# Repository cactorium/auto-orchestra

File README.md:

WIP thing, honestly just publishing just in case my laptop dies

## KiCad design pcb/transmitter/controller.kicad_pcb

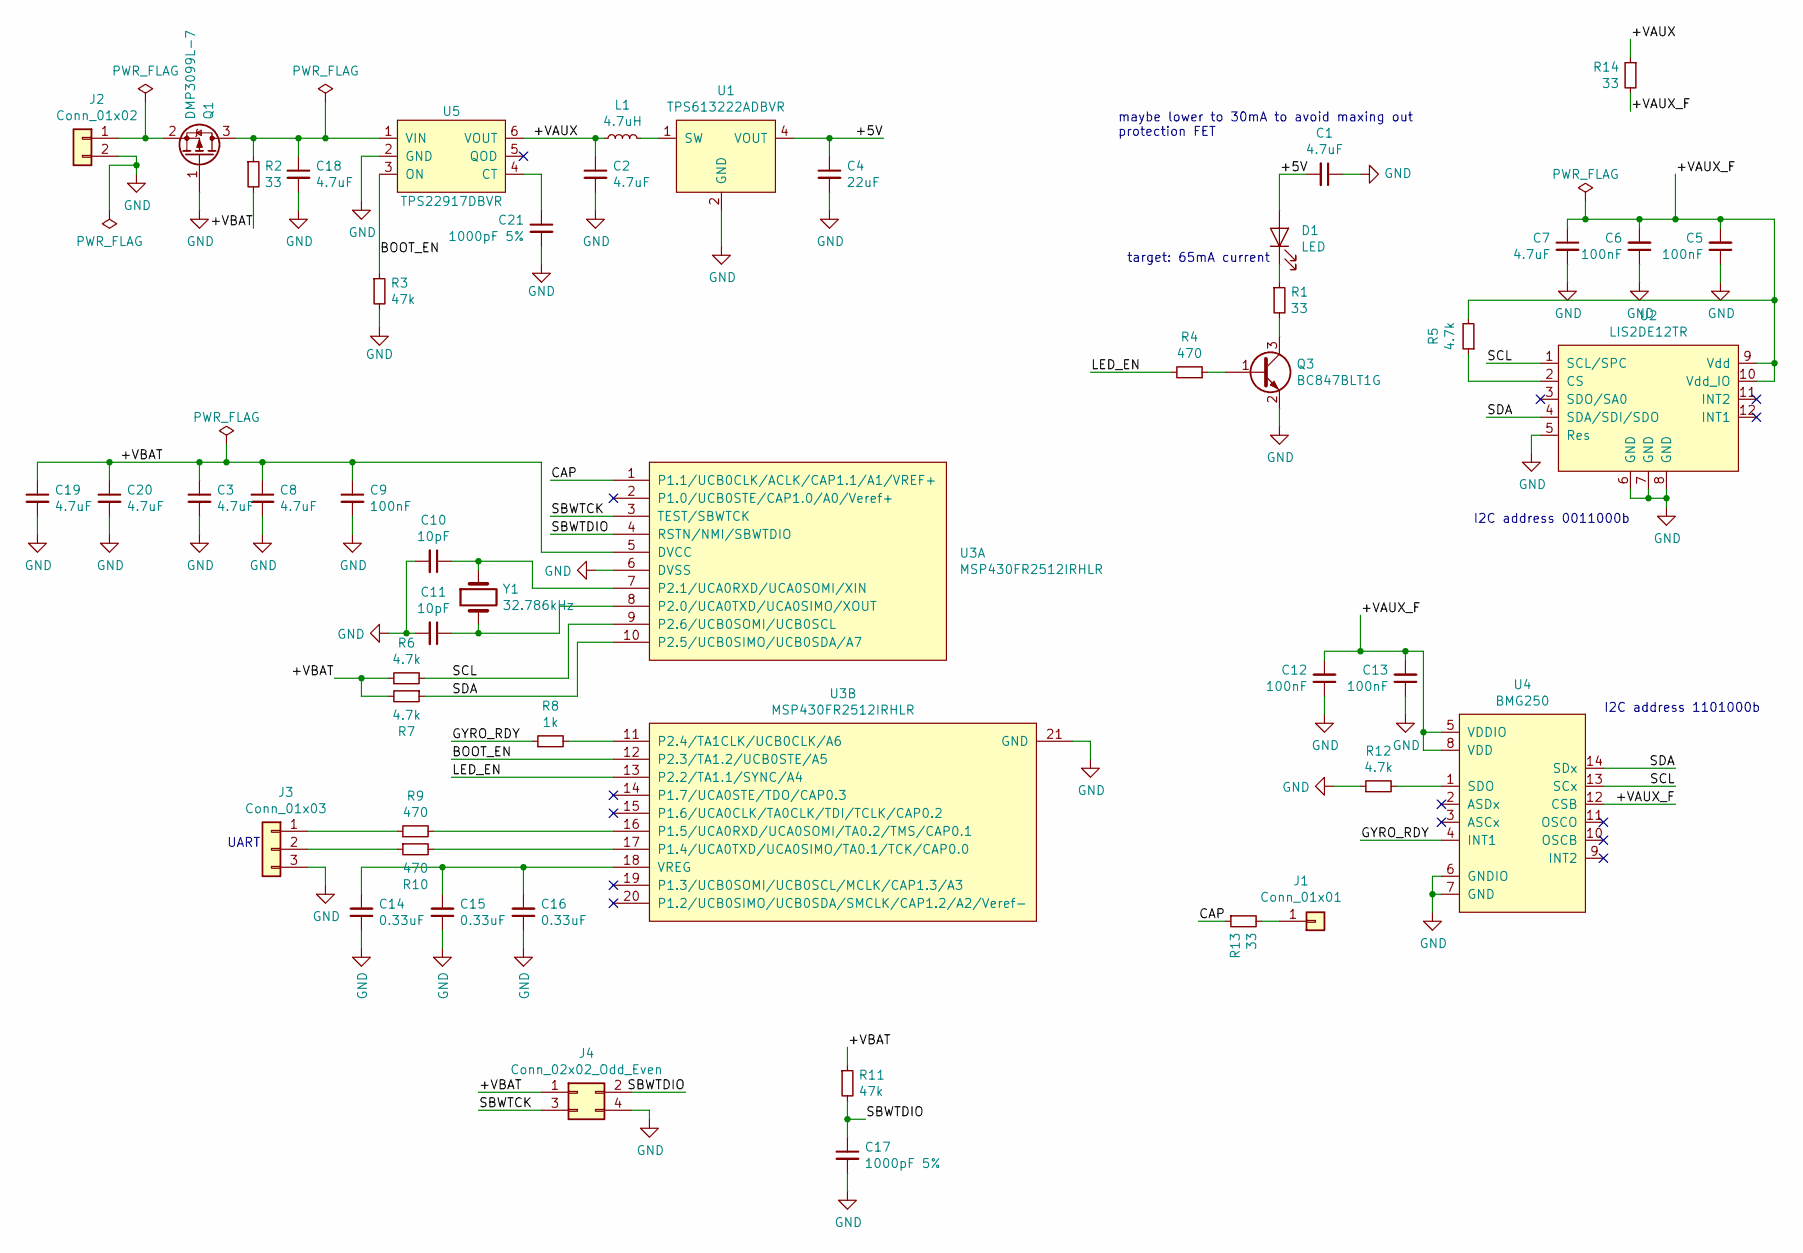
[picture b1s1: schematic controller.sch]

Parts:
C1, C2, C3, C7, C8, C18, C19, C20: 4.7uF; C_0603_HandSoldering; Mouser 810-CGB3B1X5R1A475MC
C4: 22uF; C_0805_HandSoldering; Mouser 963-LMK212BJ226MG-T
C5, C6, C9, C12, C13: 100nF; C_0402; Mouser 710-885012105018
C10, C11: 10pF; C_0402; Mouser 81-GCQ1555C1H100RB1D
C14, C15, C16: 0.33uF; C_0402; Mouser 710-885012105003
C17, C21: 1000pF 5%; C_0805_HandSoldering; Mouser 710-885012207033
D1: LED; Socket_Strip_Straight_1x02_Pitch1.27mm; Mouser 941-JB3030W00A0UC435
J1: Conn_01x01; Socket_Strip_Straight_1x01_Pitch2.54mm; Mouser NoPart
J2: Conn_01x02; Socket_Strip_Straight_1x02_Pitch1.27mm; Mouser NoPart
J3: Conn_01x03; Socket_Strip_Straight_1x03_Pitch1.27mm; Mouser NoPart
J4: Conn_02x02_Odd_Even; Socket_Strip_Straight_2x02_Pitch1.27mm; Mouser NoPart
L1: 4.7uH; Inductor_Taiyo-Yuden_NR-24xx_HandSoldering; Mouser 963-NRH2410T4R7MN
Q1: DMP3099L-7; SOT-23_Handsoldering; Mouser 621-DMP3099L-7
Q3: BC847BLT1G; SOT-23_Handsoldering; Mouser 863-BC847BLT1G
R1: 33; R_0603_HandSoldering; Mouser 755-ESR03EZPJ330
R2, R13, R14: 33; R_0603_HandSoldering
R3, R11: 47k; R_0603_HandSoldering; Mouser 603-RC0603JR-0747KL
R4, R9, R10: 470; R_0402; Mouser 791-RMC1/16S-471JTH
R5, R6, R7, R12: 4.7k; R_0402; Mouser 603-RT0402FRE074K7L
R8: 1k; R_0603_HandSoldering; Mouser 755-ESR03EZPJ102
U1: TPS613222ADBVR; SOT-23-5_HandSoldering; Mouser 595-TPS613222ADBVR
U2: LIS2DE12TR; ST_LGA12; Mouser 511-LIS2DE12TR
U3: MSP430FR2512IRHLR; TI_MSP430_VQFN20; Mouser 595-430FR2512IRHLR
U4: BMG250; Bosch_LGA14; Mouser 262-BMG250
U5: TPS22917DBVR; SOT-23-6_Handsoldering; Mouser 595-TPS22917DBVR
Y1: 32.786kHz; Crystal_DS26_d2.0mm_l6.0mm_Horizontal; Mouser 520-ECS327-6-13-X

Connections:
/+5V: C1.2, C4.1, D1.2 (A), U1.4 (VOUT)
/+VAUX: C2.1, L1.1, R14.1, U5.6 (VOUT)
/+VAUX_F: C5.2, C6.2, C7.1, C12.2, C13.2, R5.2, R14.2, U2.9 (Vdd), U2.10 (Vdd_IO), U4.5 (VDDIO), U4.8 (VDD), U4.12 (CSB)
/+VBAT: C3.1, C8.1, C9.1, C19.1, C20.1, J4.1, R2.2, R6.1, R7.2, R11.1, U3.5 (DVCC)
/BOOT_EN: R3.1, U3.12 (P2.3/TA1.2/UCB0STE/A5), U5.3 (ON)
/CAP: R13.1, U3.1 (P1.1/UCB0CLK/ACLK/CAP1.1/A1/VREF+)
/GYRO_RDY: R8.1, U4.4 (INT1)
/LED_EN: R4.2, U3.13 (P2.2/TA1.1/SYNC/A4)
/SBWTCK: J4.3, U3.3 (TEST/SBWTCK)
/SBWTDIO: C17.1, J4.2, R11.2, U3.4 (RSTN/NMI/SBWTDIO)
/SCL: R6.2, U2.1 (SCL/SPC), U3.9 (P2.6/UCB0SOMI/UCB0SCL), U4.13 (SCx)
/SDA: R7.1, U2.4 (SDA/SDI/SDO), U3.10 (P2.5/UCB0SIMO/UCB0SDA/A7), U4.14 (SDx)
GND: C1.1, C2.2, C3.2, C4.2, C5.1, C6.1, C7.2, C8.2, C9.2, C10.2, C11.2, C12.1, C13.1, C14.1, C15.1, C16.1, C17.2, C18.2, C19.2, C20.2, C21.2, J2.2, J3.3, J4.4, Q1.1 (G), Q3.2 (E), R3.2, R12.1, U1.2 (GND), U2.5 (Res), U2.6 (GND), U2.7 (GND), U2.8 (GND), U3.6 (DVSS), U3.21 (GND), U4.6 (GNDIO), U4.7 (GND), U5.2 (GND)
unnamed: C10.1, U3.7 (P2.1/UCA0RXD/UCA0SOMI/XIN), Y1.1
unnamed: C11.1, U3.8 (P2.0/UCA0TXD/UCA0SIMO/XOUT), Y1.2
unnamed: C14.2, C15.2, C16.2, U3.18 (VREG)
unnamed: C18.1, Q1.3 (D), R2.1, U5.1 (VIN)
unnamed: C21.1, U5.4 (CT)
unnamed: D1.1 (K), R1.1
unnamed: J1.1, R13.2
unnamed: J2.1, Q1.2 (S)
unnamed: J3.1, R9.1
unnamed: J3.2, R10.1
unnamed: L1.2, U1.1 (SW)
unnamed: Q3.1 (B), R4.1
unnamed: Q3.3 (C), R1.2
unnamed: R5.1, U2.2 (CS)
unnamed: R8.2, U3.11 (P2.4/TA1CLK/UCB0CLK/A6)
unnamed: R9.2, U3.16 (P1.5/UCA0RXD/UCA0SOMI/TA0.2/TMS/CAP0.1)
unnamed: R10.2, U3.17 (P1.4/UCA0TXD/UCA0SIMO/TA0.1/TCK/CAP0.0)
unnamed: R12.2, U4.1 (SDO)

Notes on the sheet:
target: 65mA current
UART
I2C address 0011000b
I2C address 1101000b
maybe lower to 30mA to avoid maxing out protection FET

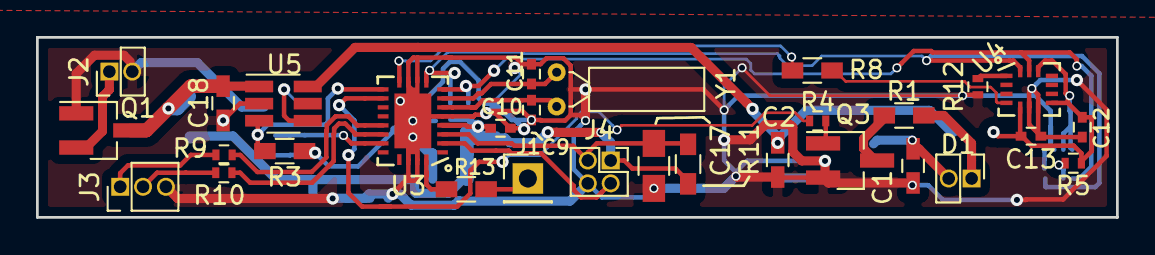
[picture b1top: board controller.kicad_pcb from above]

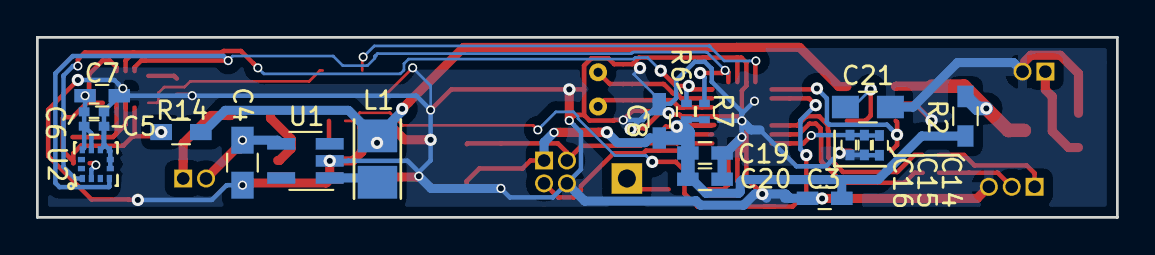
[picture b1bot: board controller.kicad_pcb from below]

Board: 2 copper layers, 60.0 x 10.0 mm, 49 parts (19 on the bottom side), 31 nets.

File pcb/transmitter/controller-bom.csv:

Reference,Quantity,Identifier,Package,Value,Tolerance,Voltage,Current,Power,PN,Mouser
"U2","1","","","LIS2DE12TR","","","","","",""
"U4","1","","","BMG250","","","","","",""
"U1","1","","","TPS613222ADBVR","","","","","",""
"J2;J1","2","","","Conn_01x02","","","","","",""
"C4","1","","","22uF","","","","","","963-LMK212BJ226MG-T"
"L1","1","","","4.7uH","","","","","",""
"Q2;Q1","2","","","Q_PMOS_DGS","","","","","",""
"R3;R8;R1","3","","","1k","","","","","","755-ESR03EZPJ102"
"C13;C12;C5;C6;C9","5","","","100nF","","","","","","710-885012105018"
"U3","1","","","MSP430FR2512IRHLR","","","","","",""
"C16;C15;C14","3","","","0.33uF","","","","","","710-885012105003"
"Y1","1","","","32.786kHz","","","","","",""
"C10;C11","2","","","10pF","","","","","","81-GCQ1555C1H100RB1D"
"C8;C2;C1;C3;C7","5","","","4.7uF","","","","","","810-CGB3B1X5R1A475MC"
"R9;R10;R4","3","","","470","","","","","","791-RMC1/16S-471JTH"
"J3","1","","","Conn_01x03","","","","","",""
"J4","1","","","Conn_02x02_Odd_Even","","","","","",""
"MH1;MH2","2","","","MountingHole","","","","","",""
"R11;R2","2","","","47k","","","","","","603-RC0603JR-0747KL"
"C17","1","","","1000pF 5%","","","","","","710-885012207033"
"R6;R7;R5","3","","","4.7k","","","","","","603-RT0402FRE074K7L"
"Q3","1","","","Q_NPN_BEC","","","","","","863-BC847BLT1G"

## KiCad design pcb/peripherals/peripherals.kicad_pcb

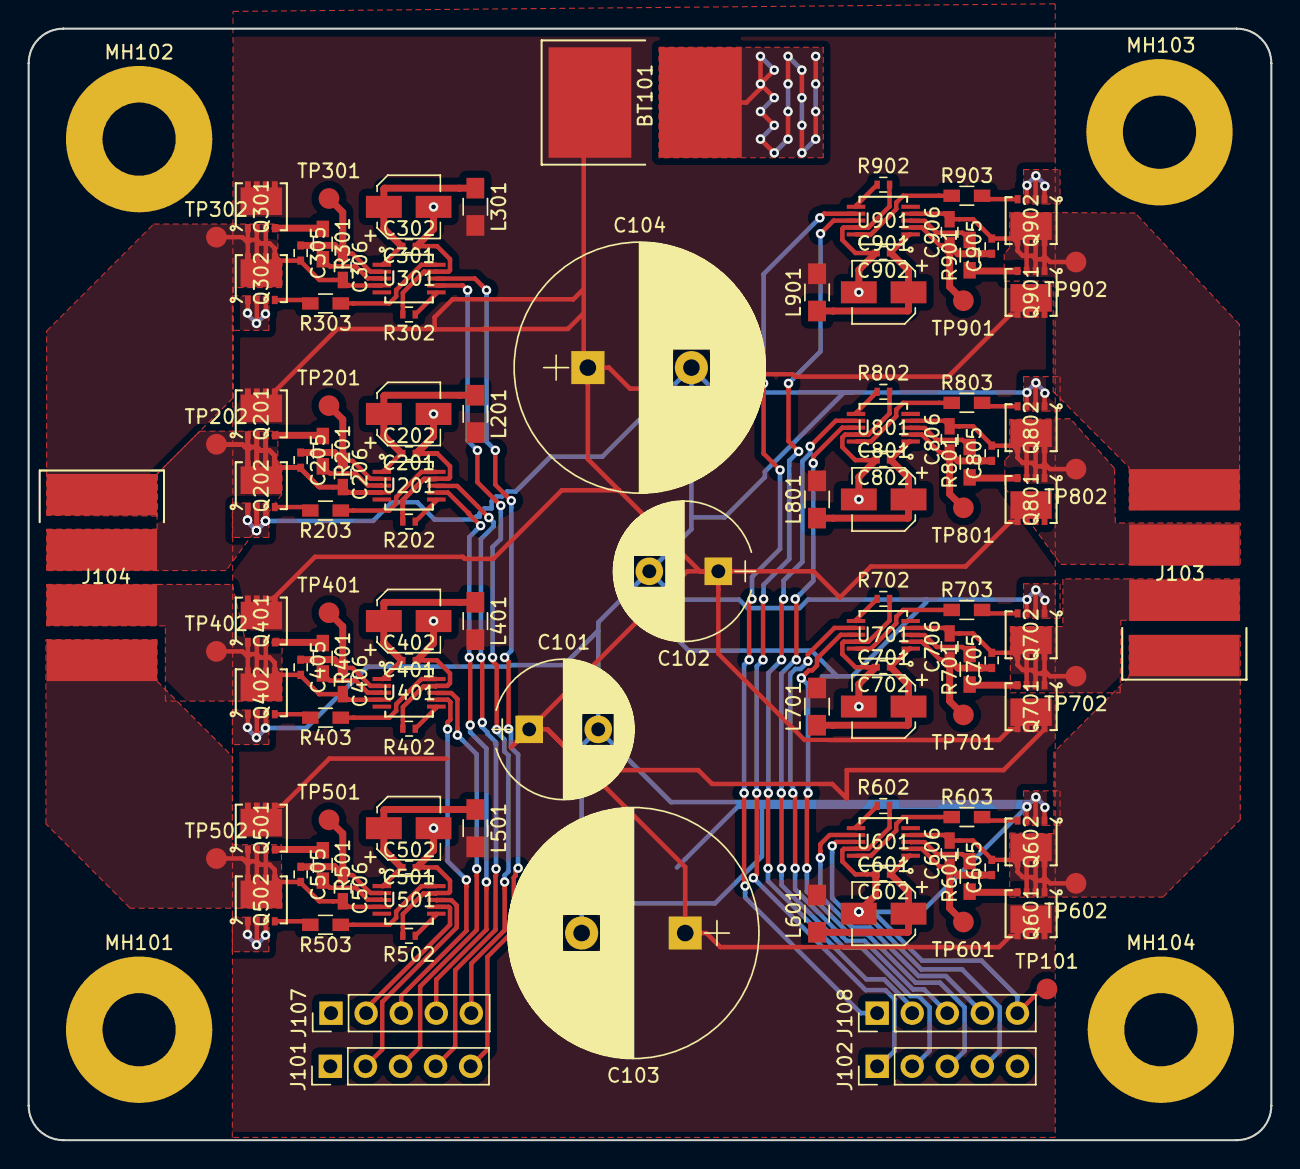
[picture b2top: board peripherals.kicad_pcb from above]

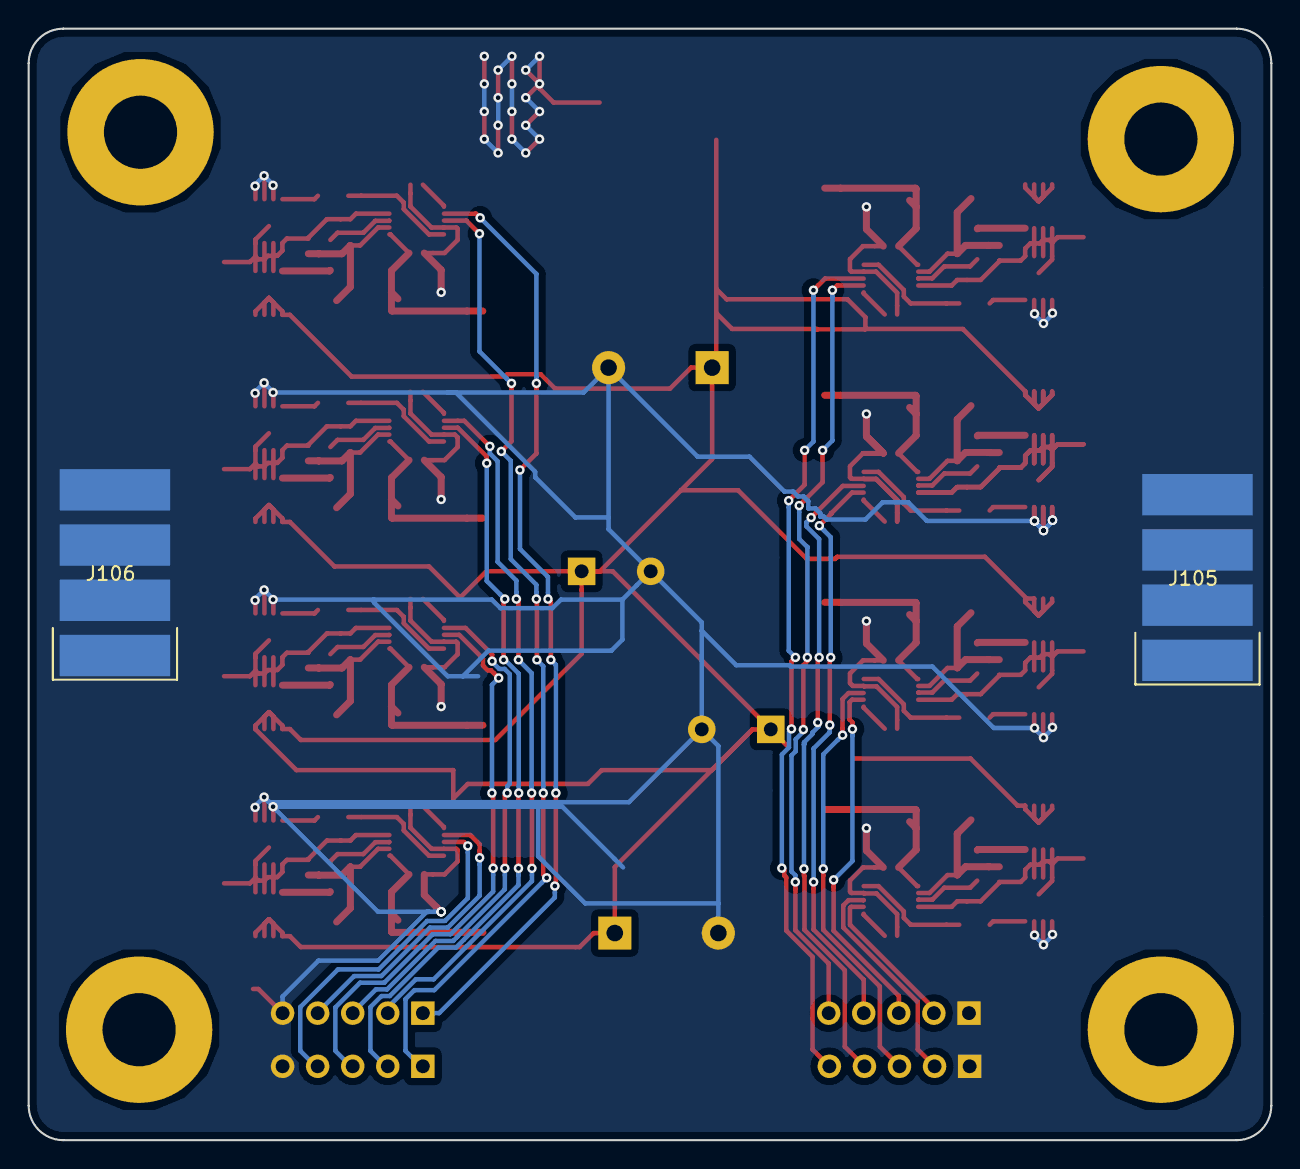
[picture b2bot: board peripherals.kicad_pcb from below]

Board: 2 copper layers, 90.0 x 80.5 mm, 122 parts (2 on the bottom side), 82 nets.

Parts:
BT101: Battery; Conn-2-8mmx6mm
C101, C102: 470uF; CP_Radial_D10.0mm_P5.00mm
C103, C104: 1000uF; CP_Radial_D18.0mm_P7.50mm
C201, C301, C401, C501, C601, C701, C801, C901: 10uF; CP_Elec_4x5.7
C202, C205, C302, C305, C402, C405, C502, C505, C602, C605, C702, C705, C802, C805, C902, C905: 100nF; C_0402
C206, C306, C406, C506, C606, C706, C806, C906: DNP 0603; C_0603_HandSoldering
J101, J102, J107, J108: Conn_01x05; Socket_Strip_Straight_1x05_Pitch2.54mm
J103, J104, J105, J106: Conn_01x04; Conn-4-8mmx3mm
L201, L301, L401, L501, L601, L701, L801, L901: 100uH; R_0805_HandSoldering
MH101, MH102, MH103, MH104: MountingHole; MountingHole_5.3mm_M5_Pad
Q201, Q202, Q301, Q302, Q401, Q402, Q501, Q502, Q601, Q602, Q701, Q702, Q801, Q802, Q901, Q902: RQ3E100BNTB; Rohm-HSMT8
R201, R203, R301, R303, R401, R403, R501, R503, R601, R603, R701, R703, R801, R803, R901, R903: 0; R_0603_HandSoldering
R202, R302, R402, R502, R602, R702, R802, R902: 100k; R_0402
TP101, TP201, TP202, TP301, TP302, TP401, TP402, TP501, TP502, TP601, TP602, TP701, TP702, TP801, TP802, TP901, TP902: TestPoint_Alt; Measurement_Point_Round-SMD-Pad_Small
U201, U301, U401, U501, U601, U701, U801, U901: DGD0506A; Diodes-MSOP10

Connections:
+BATT: BT101.1, C101.1, C102.1, C103.1, C104.1, L201.2, L301.2, L401.2, L501.2, L601.2, L701.2, L801.2, L901.2, Q201.5, Q201.6, Q201.7, Q201.8, Q301.5, Q301.6, Q301.7, Q301.8, Q401.5, Q401.6, Q401.7, Q401.8, Q501.5, Q501.6, Q501.7, Q501.8, Q601.5, Q601.6, Q601.7, Q601.8, Q701.5, Q701.6, Q701.7, Q701.8, Q801.5, Q801.6, Q801.7, Q801.8, Q901.5, Q901.6, Q901.7, Q901.8
/Sheet5B7230C3/EN: J107.4, U201.7
/Sheet5B7230C3/IN: J101.4, U201.8
/Sheet5B7230C3/OUT: C205.2, C206.2, J104.2, Q201.1, Q201.2, Q201.3, Q202.5, Q202.6, Q202.7, Q202.8, TP202.1, U201.4
/sheet5B6E6A5A/EN: J108.4, U601.7
/sheet5B6E6A5A/IN: J102.4, U601.8
/sheet5B6E6A5A/OUT: C605.2, C606.2, J103.1, Q601.1, Q601.2, Q601.3, Q602.5, Q602.6, Q602.7, Q602.8, TP602.1, U601.4
/sheet5B6E6A5B/EN: J108.3, U701.7
/sheet5B6E6A5B/IN: J102.3, U701.8
/sheet5B6E6A5B/OUT: C705.2, C706.2, J103.2, Q701.1, Q701.2, Q701.3, Q702.5, Q702.6, Q702.7, Q702.8, TP702.1, U701.4
/sheet5B6E6A5C/EN: J108.2, U801.7
/sheet5B6E6A5C/IN: J102.2, U801.8
/sheet5B6E6A5C/OUT: C805.2, C806.2, J103.3, Q801.1, Q801.2, Q801.3, Q802.5, Q802.6, Q802.7, Q802.8, TP802.1, U801.4
/sheet5B6E6A5D/EN: J108.1, U901.7
/sheet5B6E6A5D/IN: J102.1, U901.8
/sheet5B6E6A5D/OUT: C905.2, C906.2, J103.4, Q901.1, Q901.2, Q901.3, Q902.5, Q902.6, Q902.7, Q902.8, TP902.1, U901.4
/sheet5B6E69B5/EN: J107.5, U301.7
/sheet5B6E69B5/IN: J101.5, U301.8
/sheet5B6E69B5/OUT: C305.2, C306.2, J104.1, Q301.1, Q301.2, Q301.3, Q302.5, Q302.6, Q302.7, Q302.8, TP302.1, U301.4
/sheet5B6E69C3/EN: J107.3, U401.7
/sheet5B6E69C3/IN: J101.3, U401.8
/sheet5B6E69C3/OUT: C405.2, C406.2, J104.3, Q401.1, Q401.2, Q401.3, Q402.5, Q402.6, Q402.7, Q402.8, TP402.1, U401.4
/sheet5B6E69C4/EN: J107.2, U501.7
/sheet5B6E69C4/IN: J101.2, U501.8
/sheet5B6E69C4/OUT: C505.2, C506.2, J104.4, Q501.1, Q501.2, Q501.3, Q502.5, Q502.6, Q502.7, Q502.8, TP502.1, U501.4
GND: BT101.2, C101.2, C102.2, C103.2, C104.2, C201.2, C202.2, C301.2, C302.2, C401.2, C402.2, C501.2, C502.2, C601.2, C602.2, C701.2, C702.2, C801.2, C802.2, C901.2, C902.2, J101.1, J102.5, J105.1, J105.2, J105.3, J105.4, J106.1, J106.2, J106.3, J106.4, J107.1, J108.5, Q202.1, Q202.2, Q202.3, Q302.1, Q302.2, Q302.3, Q402.1, Q402.2, Q402.3, Q502.1, Q502.2, Q502.3, Q602.1, Q602.2, Q602.3, Q702.1, Q702.2, Q702.3, Q802.1, Q802.2, Q802.3, Q902.1, Q902.2, Q902.3, R202.2, R302.2, R402.2, R502.2, R602.2, R702.2, R802.2, R902.2, TP101.1, U201.9, U301.9, U401.9, U501.9, U601.9, U701.9, U801.9, U901.9
unnamed: C201.1, C202.1, L201.1, U201.1
unnamed: C205.1, C206.1, TP201.1, U201.2
unnamed: C301.1, C302.1, L301.1, U301.1
unnamed: C305.1, C306.1, TP301.1, U301.2
unnamed: C401.1, C402.1, L401.1, U401.1
unnamed: C405.1, C406.1, TP401.1, U401.2
unnamed: C501.1, C502.1, L501.1, U501.1
unnamed: C505.1, C506.1, TP501.1, U501.2
unnamed: C601.1, C602.1, L601.1, U601.1
unnamed: C605.1, C606.1, TP601.1, U601.2
unnamed: C701.1, C702.1, L701.1, U701.1
unnamed: C705.1, C706.1, TP701.1, U701.2
unnamed: C801.1, C802.1, L801.1, U801.1
unnamed: C805.1, C806.1, TP801.1, U801.2
unnamed: C901.1, C902.1, L901.1, U901.1
unnamed: C905.1, C906.1, TP901.1, U901.2
unnamed: Q201.4, R201.1
unnamed: Q202.4, R203.2
unnamed: Q301.4, R301.1
unnamed: Q302.4, R303.2
unnamed: Q401.4, R401.1
unnamed: Q402.4, R403.2
unnamed: Q501.4, R501.1
unnamed: Q502.4, R503.2
unnamed: Q601.4, R601.1
unnamed: Q602.4, R603.2
unnamed: Q701.4, R701.1
unnamed: Q702.4, R703.2
unnamed: Q801.4, R801.1
unnamed: Q802.4, R803.2
unnamed: Q901.4, R901.1
unnamed: Q902.4, R903.2
unnamed: R201.2, U201.3
unnamed: R202.1, U201.6
unnamed: R203.1, U201.10
unnamed: R301.2, U301.3
unnamed: R302.1, U301.6
unnamed: R303.1, U301.10
unnamed: R401.2, U401.3
unnamed: R402.1, U401.6
unnamed: R403.1, U401.10
unnamed: R501.2, U501.3
unnamed: R502.1, U501.6
unnamed: R503.1, U501.10
unnamed: R601.2, U601.3
unnamed: R602.1, U601.6
unnamed: R603.1, U601.10
unnamed: R701.2, U701.3
unnamed: R702.1, U701.6
unnamed: R703.1, U701.10
unnamed: R801.2, U801.3
unnamed: R802.1, U801.6
unnamed: R803.1, U801.10
unnamed: R901.2, U901.3
unnamed: R902.1, U901.6
unnamed: R903.1, U901.10

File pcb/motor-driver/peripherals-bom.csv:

Reference,Quantity,Identifier,Package,Value,Tolerance,Voltage,Current,Power,PN,Mouser
"J104;J103;J106;J105","4","","","Conn_01x04","","","","","","NoPart"
"BT101","1","","","Battery","","","","","","NoPart"
"TP101;TP201;TP202;TP301;TP302;TP401;TP402;TP501;TP502;TP601;TP602;TP701;TP702;TP801;TP802;TP901;TP902","17","","","TestPoint_Alt","","","","","","NoPart"
"J101;J107;J102;J108","4","","","Conn_01x05","","","","","","NoPart"
"MH101;MH102;MH103;MH104","4","","","MountingHole","","","","","","NoPart"
"Q201;Q202;Q301;Q302;Q401;Q402;Q501;Q502;Q601;Q602;Q701;Q702;Q801;Q802;Q901;Q902","16","","","RQ3E100BNTB","","","","","","755-RQ3E100BNTB"
"U201;U301;U401;U501;U601;U701;U801;U901","8","","","DGD0506A","","","","","","621-DGD0506AM10-13"
"R201;R203;R301;R303;R401;R403;R501;R503;R601;R603;R701;R703;R801;R803;R901;R903","16","","","0","","","","","","755-SFR03EZPJ000"
"R202;R302;R402;R502;R602;R702;R802;R902","8","","","10k","","","","","","603-RC0402JR-0710KL"
"C205;C202;C305;C302;C405;C402;C505;C502;C605;C602;C705;C702;C805;C802;C905;C902","16","","","100nF","","","","","","710-885012105018"
"C201;C301;C401;C501;C601;C701;C801;C901","8","","","10uF","","","","","","710-865080440002"
"C203;C303;C403;C503;C603;C703;C803;C903","8","","","470uF","","","","","","140-REA471M1EBK1012P"
"C204;C304;C404;C504;C604;C704;C804;C904","8","","","1000uF","","","","","","598-108SAK025M"
"L201;L301;L401;L501;L601;L701;L801;L901","8","","","100uH","","","","","","810-MLZ2012N101LT000"
"C206;C306;C406;C506;C606;C706;C806;C906","8","","","DNP 0603","","","","","","NoPart"

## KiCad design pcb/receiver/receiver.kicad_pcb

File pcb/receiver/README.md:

# OSH Park-compatible 2 Layer KiCad Template

This is a KiCad template to simplify making printed circuit boards.  

It comes with all the design rules to meet the 2-layer OSH Park specs and stackup. 

- <a href="http://docs.oshpark.com/services/two-layer/">OSH Park Two Layer Specs</a>
- <a href="http://docs.oshpark.com/design-tools/kicad">OSH Park KiCad help</a>

### Instructions

1. Open KiCad.
1. Open Preferences > Configure Paths and note the value of 'KICAD_PTEMPLATES'.
1. In KiCad, open File > New Project > New Project from Template.
1. Select the location of your new project. The name of the folder will be the name of your project.
1. The templates with folders in the 'KICAD_PTEMPLATES' are listed under 'Portable Templates" tab.
1. Select the template and click 'OK'.
1. Your project now exists, so you can open EESchema and PCBNew and design as usual.

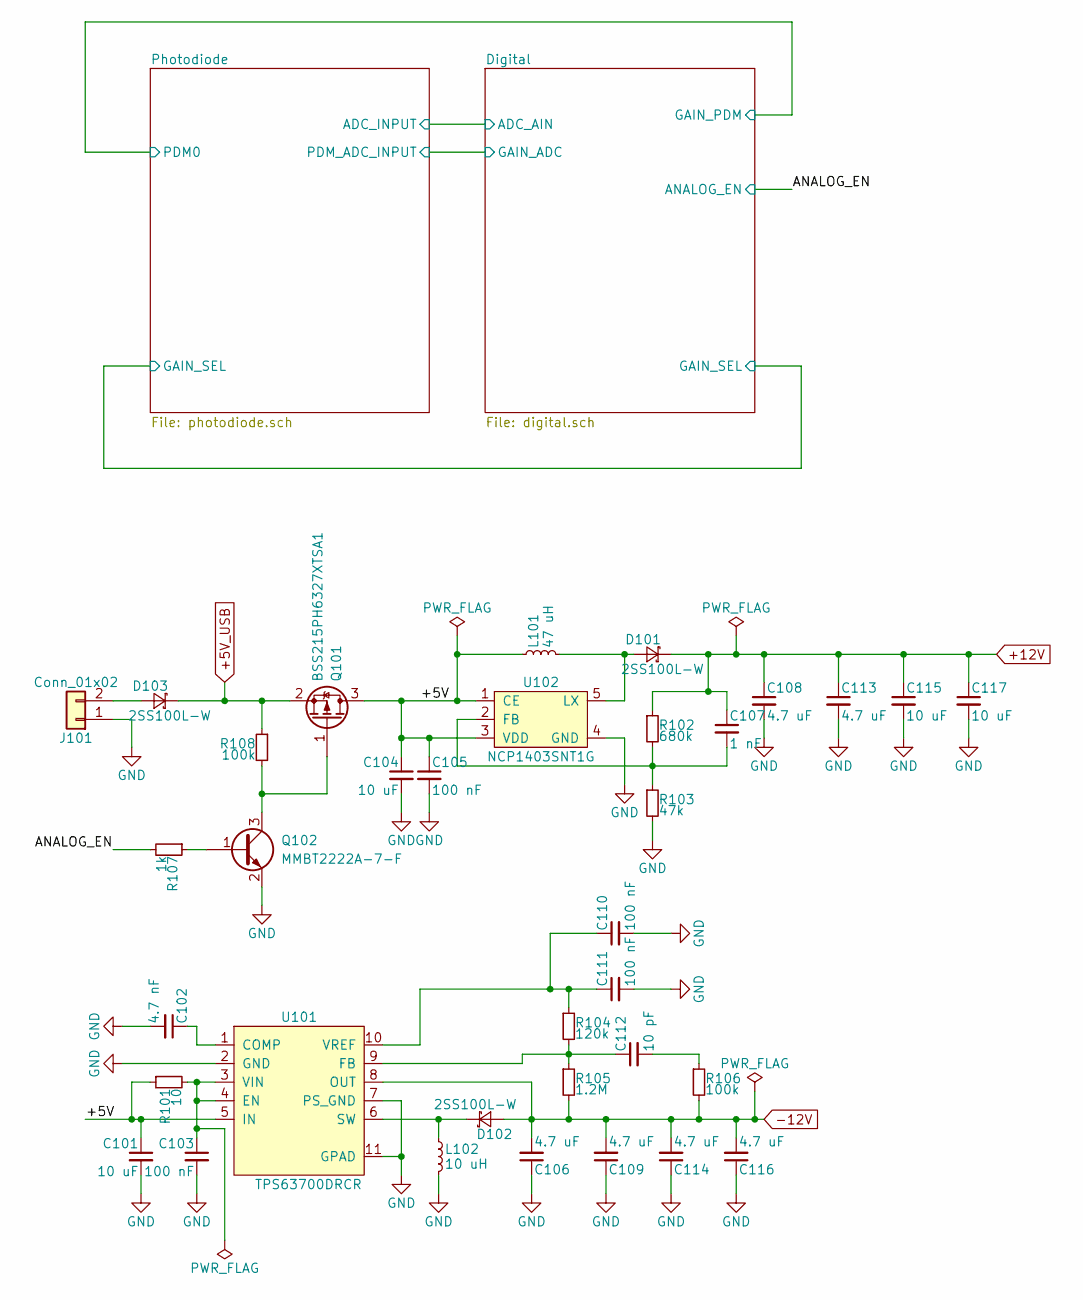
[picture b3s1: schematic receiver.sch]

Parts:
C101, C104, C115, C117: 10 uF; C_0805_HandSoldering; Mouser 81-GRM21BR61E106MA3L
C102: 4.7 nF; C_0402; Mouser 710-885012205029
C103, C105, C110, C111: 100 nF; C_0603_HandSoldering; Mouser 710-885012206071
C106, C108, C109, C113, C114, C116: 4.7 uF; CP_Elec_4x5.3; Mouser 647-UWX1E4R7MCL1
C107: 1 nF; C_0402; Mouser 710-885012205061
C112: 10 pF; C_0402; Mouser 710-885012005074
D101, D102, D103: 2SS100L-W; Rectron_SOD-123FL; Mouser 583-2SS100L-W
J101: Conn_01x02; Socket_Strip_Straight_1x02_Pitch2.54mm; Mouser NoPart
L101: 47 uH; C_0805_HandSoldering; Mouser 810-MLZ2012M470WT000
L102: 10 uH; C_0805_HandSoldering; Mouser 810-MLZ2012M100WT000
Q101: BSS215PH6327XTSA1; SOT-23_Handsoldering; Mouser 726-BSS215PH6327
Q102: MMBT2222A-7-F; SOT-23_Handsoldering; Mouser 621-MMBT2222A-F
R101: 10; C_0402; Mouser 667-ERJ-U02D10R0X
R102: 680k; R_0603_HandSoldering; Mouser 603-RC0603FR-13680KL
R103: 47k; R_0603_HandSoldering; Mouser 603-RC0603FR-0747KL
R104: 120k; R_0603_HandSoldering; Mouser 603-RC0603FR-07120KL
R105: 1.2M; R_0402; Mouser 603-RC0402JR-071M2L
R106, R108: 100k; R_0402; Mouser 603-RC0402JR-13100KL
R107: 1k; R_0603_HandSoldering; Mouser 603-RC0603JR-071KL
U101: TPS63700DRCR; TI-VSON10; Mouser 595-TPS63700DRCR
U102: NCP1403SNT1G; ON-TSOP-5; Mouser 863-NCP1403SNT1G

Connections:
+5V_USB: D103.1 (K), Q101.2 (S), R108.1; also elsewhere on the board
+12V: C107.1, C108.1, C113.1, C115.1, C117.1, D101.1 (K), R102.1; also elsewhere on the board
-12V: C106.2, C109.2, C114.2, C116.2, D102.2 (A), R105.2, R106.2, U101.8 (OUT); also elsewhere on the board
/+5V: C101.1, C104.1, C105.1, L101.1, Q101.3 (D), R101.1, U101.5 (IN), U102.1 (CE), U102.3 (VDD)
/ANALOG_EN: R107.2; also elsewhere on the board
GND: C101.2, C102.2, C103.2, C104.2, C105.2, C106.1, C108.2, C109.1, C110.2, C111.2, C113.2, C114.1, C115.2, C116.1, C117.2, J101.1, L102.2, Q102.2 (E), R103.2, U101.2 (GND), U101.7 (PS_GND), U101.11 (GPAD), U102.4 (GND); also elsewhere on the board
unnamed: C102.1, U101.1 (COMP)
unnamed: C103.1, R101.2, U101.3 (VIN), U101.4 (EN)
unnamed: C107.2, R102.2, R103.1, U102.2 (FB)
unnamed: C110.1, C111.1, R104.1, U101.10 (VREF)
unnamed: C112.1, R104.2, R105.1, U101.9 (FB)
unnamed: C112.2, R106.1
unnamed: D101.2 (A), L101.2, U102.5 (LX)
unnamed: D102.1 (K), L102.1, U101.6 (SW)
unnamed: D103.2 (A), J101.2
unnamed: Q101.1 (G), Q102.3 (C), R108.2
unnamed: Q102.1 (B), R107.1

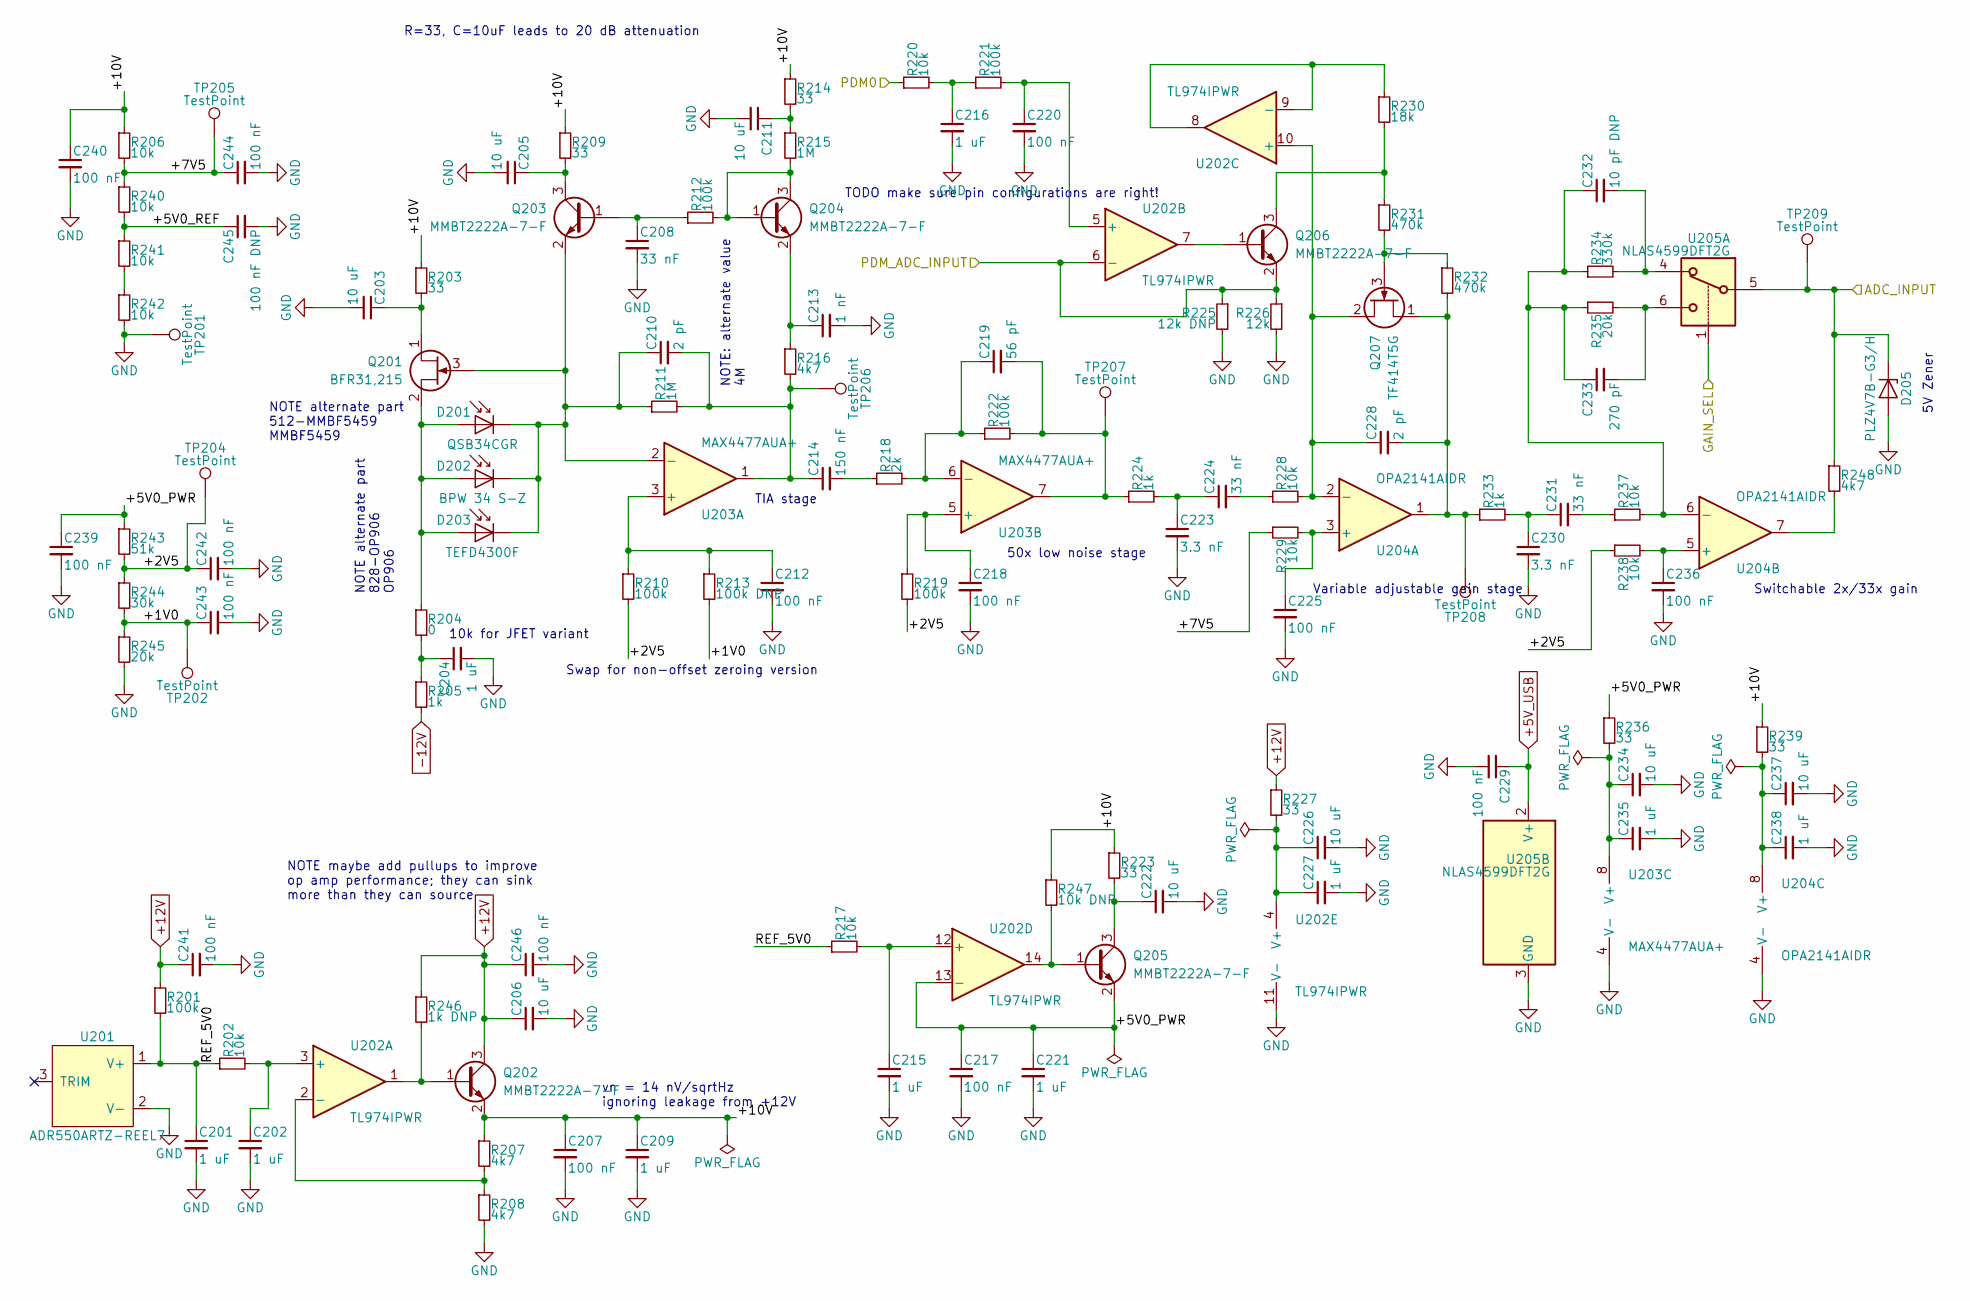
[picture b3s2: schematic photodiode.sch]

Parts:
C201, C202, C204, C209, C215, C216, C221, C227, C235, C238: 1 uF; C_0603_HandSoldering; Mouser 710-885012106022
C203, C205, C206, C211, C222, C226, C234, C237: 10 uF; C_0805_HandSoldering; Mouser 81-GRM21BR61E106MA3L
C207, C212, C217, C218, C220, C225, C229, C236, C239, C240, C241, C242, C243, C244, C246: 100 nF; C_0603_HandSoldering; Mouser 710-885012206071
C208, C224, C231: 33 nF; C_0402; Mouser 710-885012105014
C210, C228: 2 pF; C_0603_HandSoldering; Mouser 603-C0603BRNPO9BN2R0
C213: 1 nF; C_0402; Mouser 710-885012205061
C214: 150 nF; C_0603_HandSoldering; Mouser 710-885012206021
C219: 56 pF; C_0402; Mouser 77-VJ0402A560KXAPBC
C223, C230: 3.3 nF; C_0603_HandSoldering; Mouser 77-VJ0402A560KXAPBC
C232: 10 pF DNP; C_0402; Mouser 710-885012005074
C233: 270 pF; C_0402; Mouser 963-UMK105CH271JVHF
C245: 100 nF DNP; C_0603_HandSoldering; Mouser 710-885012206071
D201: QSB34CGR; Fairchild_QSB34CGR; Mouser 512-QSB34CGR
D202: BPW 34 S-Z; OSRAM_BPW34S-Z; Mouser 720-BPW34S-Z
D203: TEFD4300F; LED_D3.0mm; Mouser 78-TEFD4300F
D205: PLZ4V7B-G3/H; Vishay_DO-219AC; Mouser 78-PLZ4V7B-G3/H
Q201: BFR31,215; SOT-23_Handsoldering; Mouser 771-BFR31215
Q202, Q203, Q204, Q205, Q206: MMBT2222A-7-F; SOT-23_Handsoldering; Mouser 621-MMBT2222A-F
Q207: TF414T5G; ON_XDFN3; Mouser 863-TF414T5G
R201, R210, R212, R219, R221, R222: 100k; R_0402; Mouser 603-RC0402JR-13100KL
R202, R206, R217, R220, R228, R229, R237, R238, R240, R241, R242: 10k; R_0603_HandSoldering; Mouser 603-RC0603FR-0710KL
R203, R209, R214, R223, R227, R236, R239: 33; R_0603_HandSoldering; Mouser 755-ESR03EZPJ330
R204: 0; R_0603_HandSoldering; Mouser 755-SFR03EZPJ000
R205, R224, R233: 1k; R_0603_HandSoldering; Mouser 603-RC0603JR-071KL
R207, R208, R216, R248: 4k7; R_0603_HandSoldering; Mouser 71-CRCW06034K70JNEAC
R211, R215: 1M; R_0603_HandSoldering; Mouser 603-RC0603JR-071ML
R213: 100k DNP; R_0402; Mouser 603-RC0402JR-13100KL
R218: 2k; R_0603_HandSoldering; Mouser 603-RC0603FR-102KL
R225: 12k DNP; R_0603_HandSoldering; Mouser 603-RC0603FR-1012KL
R226: 12k; R_0603_HandSoldering; Mouser 603-RC0603FR-1012KL
R230: 18k; R_0603_HandSoldering; Mouser 603-RC0603FR-0718KL
R231, R232: 470k; R_0603_HandSoldering; Mouser 603-RC0603FR-07470KL
R234: 330k; R_0402; Mouser 603-RC0402FR-07330KL
R235, R245: 20k; R_0402; Mouser 755-SFR01MZPF2002
R243: 51k; R_0402; Mouser 603-RC0402FR-0751KL
R244: 30k; R_0402; Mouser 603-AC0402FR-0730KL
R246: 1k DNP; R_0603_HandSoldering; Mouser 603-RC0603JR-071KL
R247: 10k DNP; R_0603_HandSoldering; Mouser 603-RC0603FR-0710KL
TP201, TP202, TP204, TP205, TP206, TP207, TP208, TP209: TestPoint; Measurement_Point_Round-SMD-Pad_Small; Mouser NoPart
U201: ADR550ARTZ-REEL7; SOT-23_Handsoldering; Mouser 584-ADR550ARTZ-R7
U202: TL974IPWR; TI-SOIC14; Mouser 595-TL974IPWR
U203: MAX4477AUA+; Maxim-uMAX8; Mouser 700-MAX4477AUA
U204: OPA2141AIDR; TI-SOIC8; Mouser 595-OPA2141AIDR
U205: NLAS4599DFT2G; On-SOT363; Mouser 863-NLAS4599DFT2G

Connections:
+5V_USB: C229.1, U205.2 (V+); also elsewhere on the board
+12V: C206.1, C241.1, C246.1, Q202.3 (C), R201.1, R227.1, R246.1; also elsewhere on the board
-12V: R205.2; also elsewhere on the board
/Digital/ADC_AIN: D205.1 (K), R248.1, TP209.1, U205.5; also elsewhere on the board
/Digital/GAIN_ADC: Q206.2 (E), R225.1, R226.1, U202.6 (-); also elsewhere on the board
/Digital/GAIN_PDM: R220.1; also elsewhere on the board
/Digital/GAIN_SEL: U205.1; also elsewhere on the board
/Photodiode/+1V0: C243.1, R213.2, R244.2, R245.1, TP202.1
/Photodiode/+2V5: C242.1, R210.2, R219.2, R238.1, R243.2, R244.1, TP204.1
/Photodiode/+5V0_PWR: C217.1, C221.1, C239.1, Q205.2 (E), R236.1, R243.1, U202.13 (-)
/Photodiode/+5V0_REF: C245.1, R240.2, R241.1
/Photodiode/+7V5: C244.1, R206.2, R229.1, R240.1, TP205.1
/Photodiode/+10V: C207.1, C209.1, C240.1, Q202.2 (E), R203.1, R206.1, R207.1, R209.1, R214.1, R223.1, R239.1, R247.1
/Photodiode/REF_5V0: C201.1, R201.2, R202.1, R217.1, U201.1 (V+)
GND: C201.2, C202.2, C203.2, C204.2, C205.2, C206.2, C207.2, C208.2, C209.2, C211.2, C212.2, C213.2, C215.2, C216.2, C217.2, C218.2, C220.2, C221.2, C222.2, C223.2, C225.2, C226.2, C227.2, C229.2, C230.2, C234.2, C235.2, C236.2, C237.2, C238.2, C239.2, C240.2, C241.2, C242.2, C243.2, C244.2, C245.2, C246.2, D205.2 (A), R208.2, R225.2, R226.2, R242.2, R245.2, TP201.1, U201.2 (V-), U202.11 (V-), U203.4 (V-), U204.4 (V-), U205.3 (GND); also elsewhere on the board
unnamed: C202.1, R202.2, U202.3 (+)
unnamed: C203.1, Q201.1 (D), R203.2
unnamed: C204.1, R204.2, R205.1
unnamed: C205.1, Q203.3 (C), R209.2
unnamed: C208.1, Q203.1 (B), R212.1
unnamed: C210.1, D201.1 (K), D202.1 (K), D203.1 (K), Q201.3 (G), Q203.2 (E), R211.1, U203.2 (-)
unnamed: C210.2, C214.1, R211.2, R216.2, TP206.1, U203.1
unnamed: C211.1, R214.2, R215.1
unnamed: C212.1, R210.1, R213.1, U203.3 (+)
unnamed: C213.1, Q204.2 (E), R216.1
unnamed: C214.2, R218.1
unnamed: C215.1, R217.2, U202.12 (+)
unnamed: C216.1, R220.2, R221.1
unnamed: C218.1, R219.1, U203.5 (+)
unnamed: C219.1, R218.2, R222.1, U203.6 (-)
unnamed: C219.2, R222.2, R224.1, TP207.1, U203.7
unnamed: C220.1, R221.2, U202.5 (+)
unnamed: C222.1, Q205.3 (C), R223.2
unnamed: C223.1, C224.1, R224.2
unnamed: C224.2, R228.1
unnamed: C225.1, R229.2, U204.3 (+)
unnamed: C226.1, C227.1, R227.2, U202.4 (V+)
unnamed: C228.1, Q207.2 (D), R228.2, U202.10 (+), U204.2 (-)
unnamed: C228.2, Q207.1 (S), R232.2, R233.1, TP208.1, U204.1
unnamed: C230.1, C231.1, R233.2
unnamed: C231.2, R237.1
unnamed: C232.1, C233.1, R234.1, R235.1, R237.2, U204.6 (-)
unnamed: C232.2, R234.2, U205.4
unnamed: C233.2, R235.2, U205.6
unnamed: C234.1, C235.1, R236.2, U203.8 (V+)
unnamed: C236.1, R238.2, U204.5 (+)
unnamed: C237.1, C238.1, R239.2, U204.8 (V+)
unnamed: D201.2 (A), D202.2 (A), D203.2 (A), Q201.2 (S), R204.1
unnamed: Q202.1 (B), R246.2, U202.1
unnamed: Q204.1 (B), Q204.3 (C), R212.2, R215.2
unnamed: Q205.1 (B), R247.2, U202.14
unnamed: Q206.1 (B), U202.7
unnamed: Q206.3 (C), R230.2, R231.1
unnamed: Q207.3 (G), R231.2, R232.1
unnamed: R207.2, R208.1, U202.2 (-)
unnamed: R230.1, U202.8, U202.9 (-)
unnamed: R241.2, R242.1
unnamed: R248.2, U204.7

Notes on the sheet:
10k for JFET variant
TODO make sure pin configurations are right!
50x low noise stage
TIA stage
Variable adjustable gain stage
Switchable 2x/33x gain
Swap for non-offset zeroing version
R=33, C=10uF leads to 20 dB attenuation
vn = 14 nV/sqrtHz ignoring leakage from +12V
NOTE maybe add pullups to improve op amp performance; they can sink more than they can source
5V Zener
NOTE alternate part 512-MMBF5459 MMBF5459
NOTE: alternate value 4M
NOTE alternate part 828-OP906 OP906
